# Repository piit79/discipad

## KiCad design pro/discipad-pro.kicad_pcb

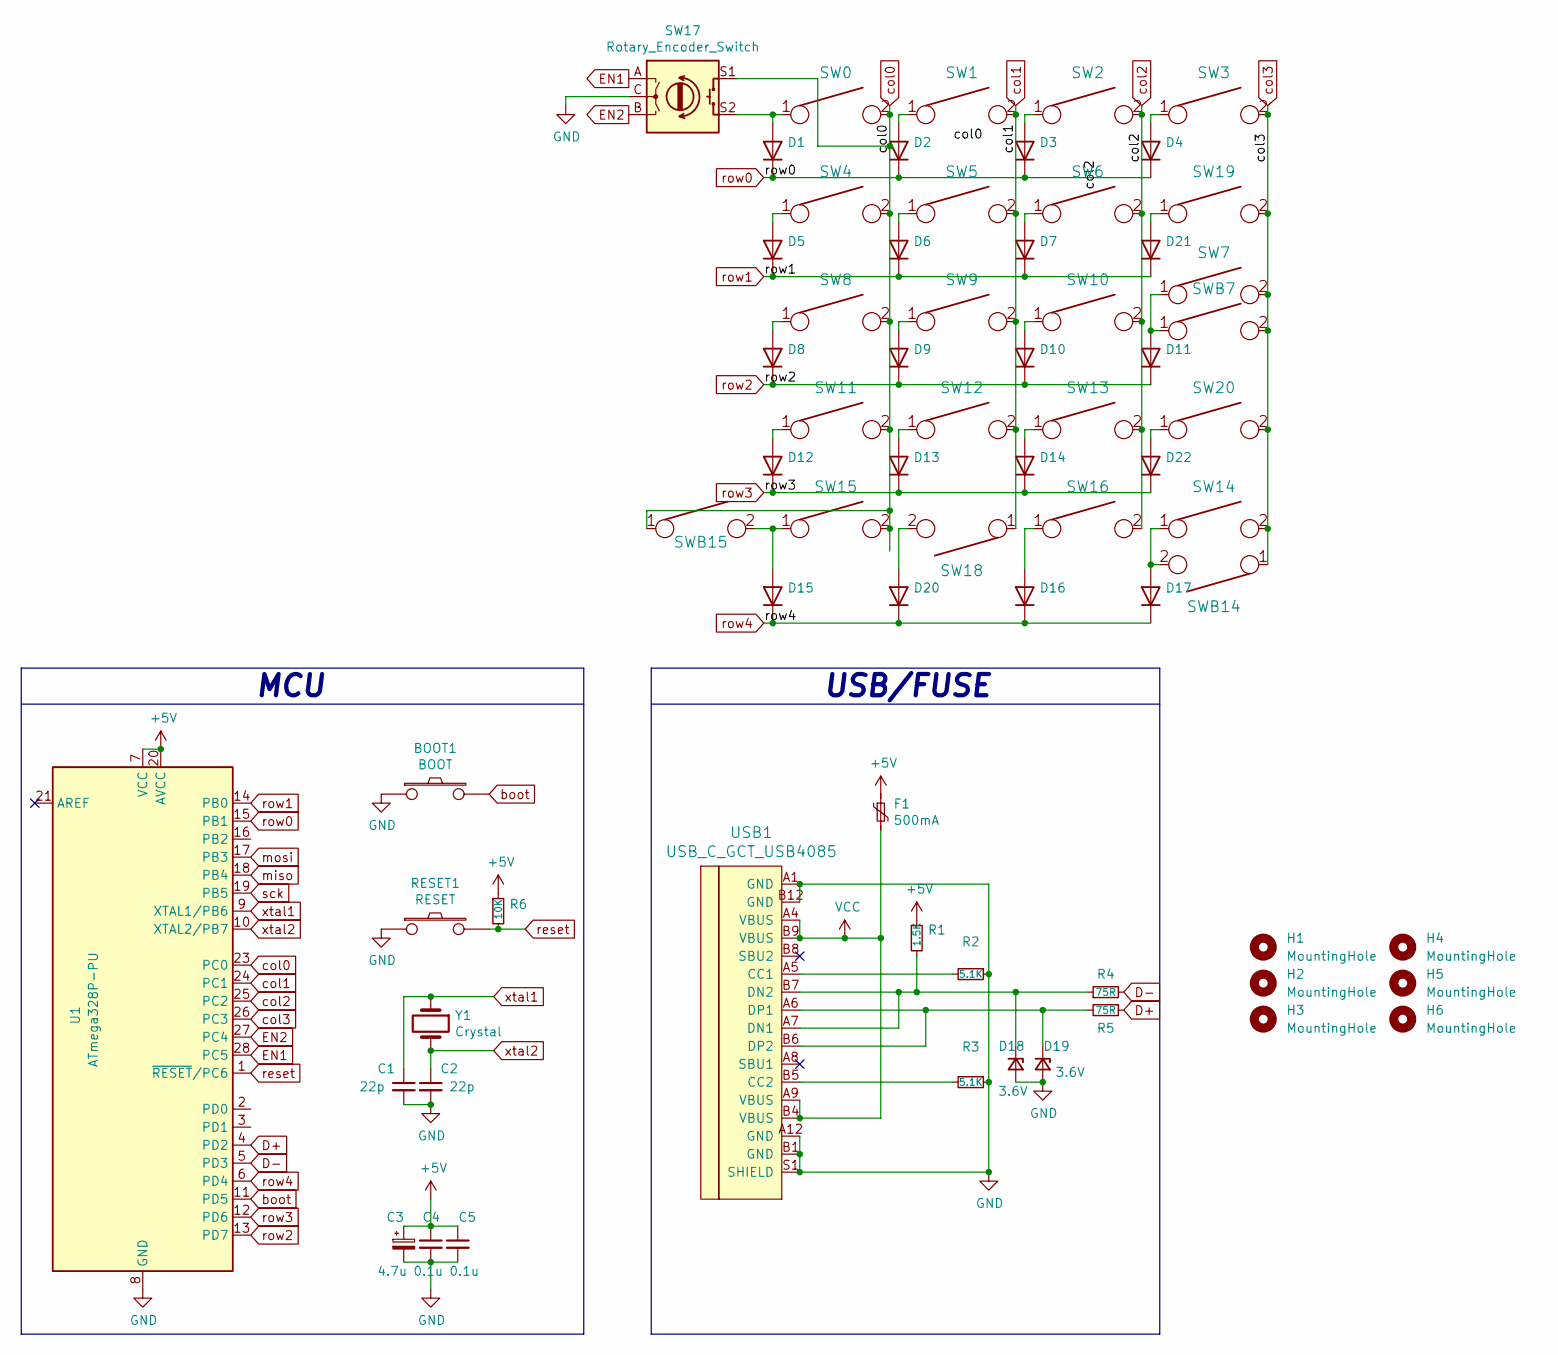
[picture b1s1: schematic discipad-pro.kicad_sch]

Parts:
BOOT1: BOOT; SW_PUSH_6mm
C1, C2: 22p; C_Disc_D3.0mm_W1.6mm_P2.50mm
C3: 4.7u; CP_Radial_D4.0mm_P1.50mm
C4, C5: 0.1u; C_Disc_D4.3mm_W1.9mm_P5.00mm
D1, D2, D3, D4, D5, D6, D7, D8, D9, D10, D11, D12, D13, D14, D15, D16, D17, D20, D21, D22: D_DO-35_SOD27_P5.08mm_Horizontal
D18, D19: 3.6V; ZD_DO-35_SOD27_P5.08mm_Horizontal_smaller
F1: 500mA; polyfuse_5.1mm
H1, H2, H3, H4, H5, H6: MountingHole; MountingHole_2.2mm_M2_Pad
R1: 1.5K; R_Axial_DIN0204_L3.6mm_D1.6mm_P5.08mm_Horizontal
R2, R3: 5.1K; R_Axial_DIN0204_L3.6mm_D1.6mm_P5.08mm_Horizontal
R4, R5: 75R; R_Axial_DIN0204_L3.6mm_D1.6mm_P5.08mm_Horizontal
R6: 10K; R_Axial_DIN0204_L3.6mm_D1.6mm_P5.08mm_Horizontal
RESET1: RESET; SW_PUSH_6mm
SW0, SW1, SW2, SW3, SW4, SW5, SW6, SW8, SW9, SW10, SW11, SW12, SW13, SW16, SW18, SW19, SW20: KEYSW; Kailh_MX_Socket-swapped-pads
SW7, SW14, SW15: KEYSW; Kailh_MX_Socket-2u-swapped-pads-reversed-stabilizer
SW17: Rotary_Encoder_Switch; RotaryEncoder_Alps_EC11E-Switch_Vertical_H20mm-for-MX
SWB7, SWB14, SWB15: KEYSW; Kailh_MX_Socket-swapped-pads
U1: ATmega328P-PU; DIP-28_W7.62mm
USB1: USB_C_GCT_USB4085; USB_C_GCT_USB4085-offset-pads
Y1: Crystal; Crystal_HC49-4H_Vertical

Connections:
+5V: C3.1, C4.1, C5.1, F1.1, R1.1, R6.1, U1.7 (VCC), U1.20 (AVCC)
D+: R5.1, U1.4 (PD2)
D-: R4.2, U1.5 (PD3)
EN1: SW17.A, U1.28 (PC5)
EN2: SW17.B, U1.27 (PC4)
GND: BOOT1.1, C1.2, C2.2, C3.2, C4.2, C5.2, D18.2 (A), D19.2 (A), R2.1, R3.1, RESET1.1, SW17.C, U1.8 (GND), U1.22 (GND), USB1.A1 (GND), USB1.A12 (GND), USB1.B1 (GND), USB1.B12 (GND), USB1.S1 (SHIELD)
unnamed: D1.2 (A), SW0.1, SW17.S2
unnamed: D2.2 (A), SW1.1
unnamed: D3.2 (A), SW2.1
unnamed: D4.2 (A), SW3.1
unnamed: D5.2 (A), SW4.1
unnamed: D6.2 (A), SW5.1
unnamed: D7.2 (A), SW6.1
unnamed: D8.2 (A), SW8.1
unnamed: D9.2 (A), SW9.1
unnamed: D10.2 (A), SW10.1
unnamed: D11.2 (A), SW7.1, SWB7.1
unnamed: D12.2 (A), SW11.1
unnamed: D13.2 (A), SW12.1
unnamed: D14.2 (A), SW13.1
unnamed: D15.2 (A), SW15.1, SWB15.2
unnamed: D16.2 (A), SW16.1
unnamed: D17.2 (A), SW14.1, SWB14.2
unnamed: D18.1 (K), R1.2, R4.1, USB1.A7 (DN1), USB1.B7 (DN2)
unnamed: D19.1 (K), R5.2, USB1.A6 (DP1), USB1.B6 (DP2)
unnamed: D20.2 (A), SW18.2
unnamed: D21.2 (A), SW19.1
unnamed: D22.2 (A), SW20.1
unnamed: R2.2, USB1.A5 (CC1)
unnamed: R3.2, USB1.B5 (CC2)
VCC: F1.2, USB1.A4 (VBUS), USB1.A9 (VBUS), USB1.B4 (VBUS), USB1.B9 (VBUS)
boot: BOOT1.2, U1.11 (PD5)
col0: SW0.2, SW4.2, SW8.2, SW11.2, SW15.2, SW17.S1, SWB15.1, U1.23 (PC0)
col1: SW1.2, SW5.2, SW9.2, SW12.2, SW18.1, U1.24 (PC1)
col2: SW2.2, SW6.2, SW10.2, SW13.2, SW16.2, U1.25 (PC2)
col3: SW3.2, SW7.2, SW14.2, SW19.2, SW20.2, SWB7.2, SWB14.1, U1.26 (PC3)
miso: U1.18 (PB4)
mosi: U1.17 (PB3)
reset: R6.2, RESET1.2, U1.1 (~RESET/PC6)
row0: D1.1 (K), D2.1 (K), D3.1 (K), D4.1 (K), U1.15 (PB1)
row1: D5.1 (K), D6.1 (K), D7.1 (K), D21.1 (K), U1.14 (PB0)
row2: D8.1 (K), D9.1 (K), D10.1 (K), D11.1 (K), U1.13 (PD7)
row3: D12.1 (K), D13.1 (K), D14.1 (K), D22.1 (K), U1.12 (PD6)
row4: D15.1 (K), D16.1 (K), D17.1 (K), D20.1 (K), U1.6 (PD4)
sck: U1.19 (PB5)
xtal1: C1.1, U1.9 (XTAL1/PB6), Y1.1
xtal2: C2.1, U1.10 (XTAL2/PB7), Y1.2

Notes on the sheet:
USB/FUSE
MCU

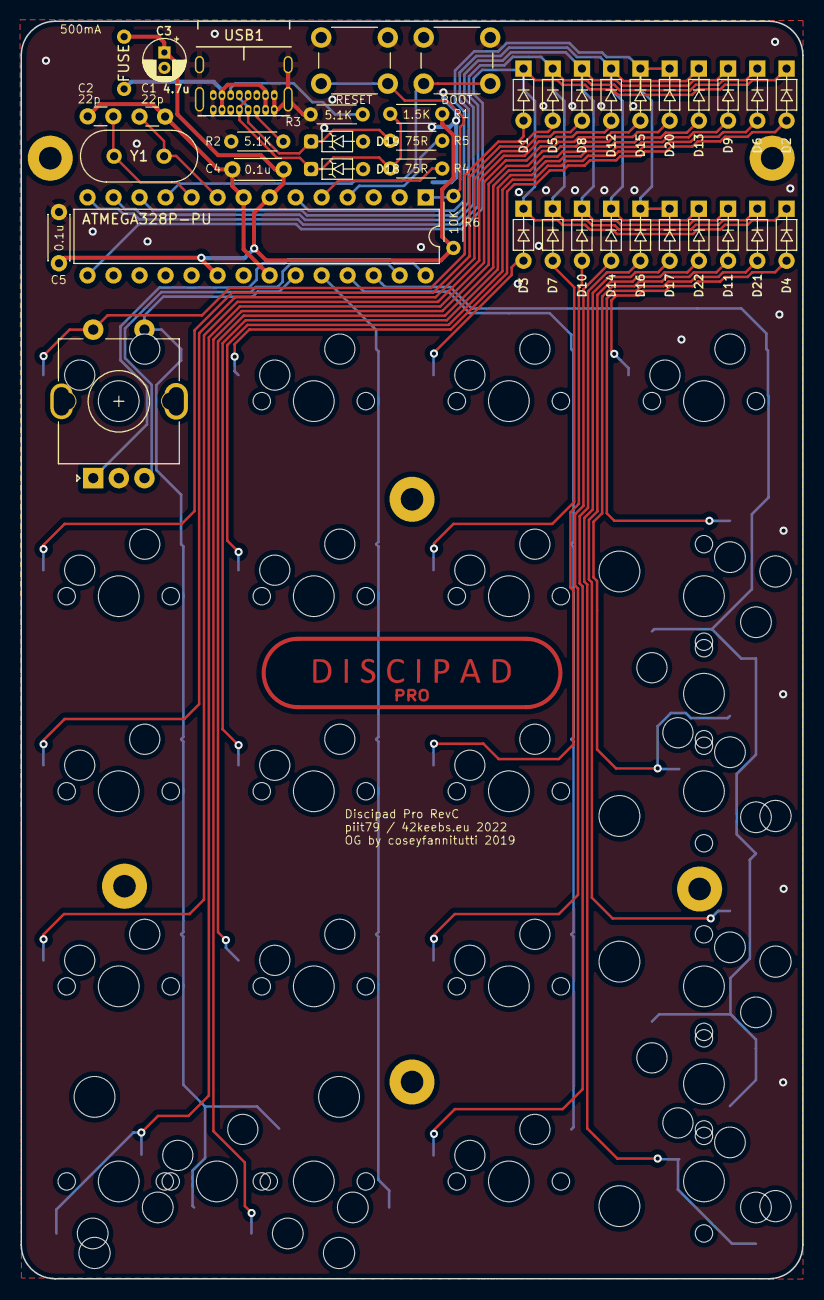
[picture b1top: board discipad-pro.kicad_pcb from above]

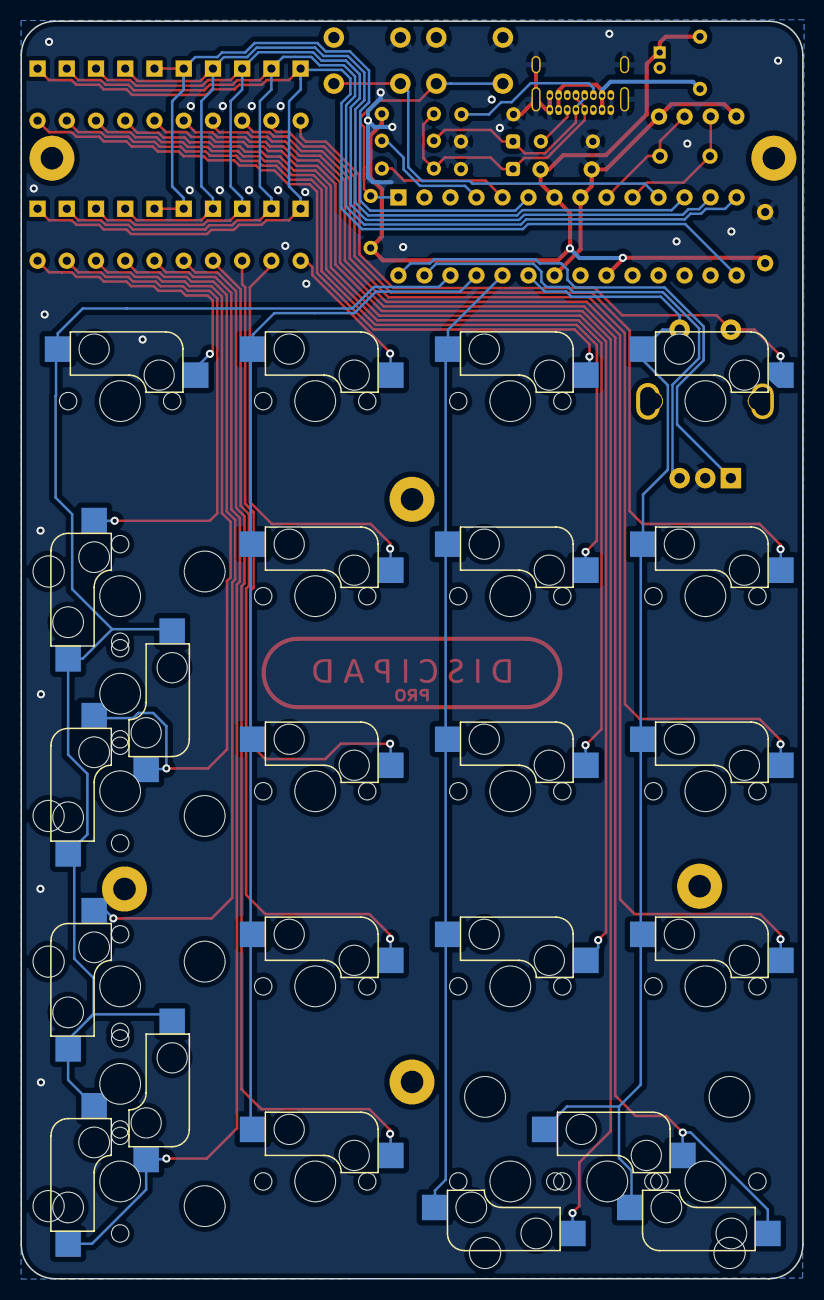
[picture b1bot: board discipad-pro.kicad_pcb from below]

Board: 2 copper layers, 76.3 x 122.8 mm, 69 parts (23 on the bottom side), 44 nets.

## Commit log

2021-03-29 Add switch plate
2021-03-29 Add Discipad Pro with Kailh hostswap sockets
2021-03-29 Update gerber files and zips
2021-10-17 Remove schematic/PCB backups; add .gitignore
2021-10-17 Add rotary encoder support to Discipad Pro
2021-10-17 Update bottom with plated logo and JLCPCB order placeholder
2021-10-17 Update plate with JLCPCB order placeholder
2022-07-12 Remove fp-info-cache from the repo and add to .gitignore
2022-07-12 Add support for splitting all 2u keys; improve ground connection
2022-07-12 Add 42. Keebs KiCad library as submodule
2022-07-12 Switch to USB-C and diode footprints from the 42. Keebs library
2022-07-12 Plate RevC: update with split 2u keys
2022-07-12 Bottom RevC: move cone feet holes further apart for better stability
2022-07-12 Remove Gerber files from the repository and add them to .gitignore
    Gerbers belong to GitHub releases
2023-10-02 Add build and flashing guide PDFs from Internet Archive; update links in README
